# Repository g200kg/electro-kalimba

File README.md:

# electro-kalimba
ElectroKalimba EK-002

## About Kalimba

The kalimba is an African folk instrument. It is a simple instrument that is also called a "thumb piano" and produces sound by plucking metal pieces lined up on a board with your fingers. There are various styles and names depending on the country and region,  but the one with 17 keys is generally distributed as "kalimba" today.  

The keys are arranged so that the pitch is the lowest in the center, and the pitch becomes higher as you move toward the edges, alternating left and right. On the piano, there are only white keys, and there are no keys on the keyboard that correspond to the semitones of the black keys. 

The current kalimba produces a clear, almost sine-wave, music box-like sound from the vibrating metal pieces, but the original use of the kalimba was to add a jittery noise by wrapping a bit of wire around the metal pieces.

---

カリンバはアフリカの民族楽器で、板の上に並んだ金属片を指ではじいて音を出す「親指ピアノ」などとも呼ばれるシンプルな楽器です。国や地方によって様々な様式や名前のものがありますが、現在一般的には 17 鍵のものが「カリンバ」として流通しています。  

キーの配置は中心が一番低い音程になっていて左右交互に端に行くにしたがって高い音になっていきます。音程はピアノで言えば白鍵のみしかなく、黒鍵の半音に相当する鍵盤はありません。  

現在のカリンバは金属片が振動するほぼサイン波の澄んだオルゴールのような音が鳴りますが、元々のカリンバの使い方としては金属片に少し針金を巻きつけるなどによってジージーと鳴るノイズを加えたりします。

## Usage

This "ElectroKalimba" can be played like a normal kalimba, but while a normal kalimba makes a sound by flicking a key, this electronic kalimba makes a sound when you press a key, so the feeling of playing is slightly different.

If nothing is connected to the LineOut terminal, sound will be output from the built-in speaker. The built-in speaker is muted when the LineOut terminal is used. Connect a 2-pole (monaural) or 3-pole (stereo) mini plug to the LineOut terminal. If you connect a plug with 4 or more pins, it may not work properly.

The battery is rechargeable. Charging is done using the Charge MicroUSB terminal on the front of the main unit. The Debug MicroUSB at the top left of the main unit is the USB connector of the Nucleo board used internally, and is used when writing/debugging programs.

---

この ElectroKalimba は普通のカリンバのように演奏できますが、普通のカリンバがキーをはじいて音を出すのに対し、この電子カリンバはキーを押し込んだ時に音を出しますので、演奏の感覚は微妙に異なるかも知れません。

LineOut 端子に何も接続していない場合は内蔵スピーカーから音がでます。LineOut 端子使用時は内蔵スピーカーはミュートされます。LineOut 端子には 2 極(モノラル)または 3 極 (ステレオ) のミニプラグを接続してください。4 極以上のプラグを接続した場合は正常に動作しない場合があります。

電池は充電式です。充電は本体手前にある Charge MicroUSB 端子で行います。本体左上にある Debug MicroUSB は内部で使用している Nucleo ボードの USB コネクタで、プログラムの書き込み/デバッグを行う際に使用します。

| 端子            | 説明                              |
|:---------------:|:---------------------------------:|
| Charge MicroUSB | 充電用 USB                        |
| Debug MicroUSB  | プログラム書き込み/デバッグ用 USB |
| Power Switch    | 電源スイッチ                      |
| Tuning          | チューニング                      |
| Waveform        | 音色設定　詳細は下の図            |
| Sustain         | サステイン　音の伸び方の設定      |
| Volume          | 音量設定                          |
| Line Out        | ライン出力                        |

## Demo Movie  

https://youtu.be/vXB684UsEok  

# Repository

This repository contains design data for the musical instrument "ElectroKalimba".
Contains schematic, software source code, and 3D data of mechanical design.

---

このリポジトリは楽器、"電子カリンバ" の設計データです。
回路図、ソフトウェアのソースコード、機構設計の 3D データを含みます。

# Directories

Contains the following files  
  
   Blender - Mechanism design data - Blender 4.0.2  
   KiCad - Circuit/Board Design Data - KiCad 7.0  
   STM32CubeIDE - Software Design Data - STM32CubeIDE 1.13.2  

---

以下のファイルが含まれています
  
  Blender - 機構設計データ - Blender 4.0.2  
  KiCad - 回路/基板設計データ - KiCad 7.0  
  STM32CubeIDE - ソフトウェア設計データ - STM32CubeIDE 1.13.2  

## Blender files

The Blender directory contains 3D data for the "Blender" housing. The following four parts are required for the casing.  
  
Case_Top: Keyboard section and top of main body  
Case_Mid: Lower part of the main body  
Case_SP_Ring: Speaker front cover  
Case_Bottom: Bottom  
Case_SP_Cap: Speaker bottom cover  

All parts can be printed with no or very little support. When printing Case_Top, Case_Mid, and Case_SP_Ring, rotate them upside down. Printing confirmed with Creality K1 without brim or raft.  

In the design data, numerical values are specified in "cm" units. Please scale as necessary when printing.  

The "*.stl" file is an STL export of each part, already scaled to "mm" units.  

The 3D printer must be able to print at least 140 x 147 mm.  

---

Blender ディレクトリには "Blender" 用の筐体の 3D データが収められています。
筐体として必要なのは次の4つのパーツになります。

* Case_Top : 鍵盤部と本体上部
* Case_Mid : 本体下部
* Case_SP_Ring : スピーカー前面のカバー
* Case_Bottom : 底面
* Case_SP_Cap : スピーカー底部のカバー

全てのパーツはサポートなし、あるいはほぼサポートなしで印刷できま\す。Case_Top、Case_Mid、Case_SP_Ring は印刷時には回転して上下を逆にしてください。
Creality K1 でブリム、ラフトなしで印刷を確認しています。

設計データ上は "cm" 単位で数値指定しています。印刷時に必要に応じてスケーリングしてください。

"*.stl" ファイルは各パーツを STL として書き出したもので、既にスケーリングされて "mm" 単位になっています。

3D プリンターは少なくとも 140 x 147 mm のサイズを造形できる必要があります。

## KiCad files

PDF 化した回路図 と KiCad 7.0.2 用のファイルです。

---

Schametic PDF and files for KiCad 7.0.2.

* EK002-pcb.pdf Schematic PDF.
* EK002.kicad_sch Kicad Schematic
* EK002.kicad_pcb Kicad Artwork

## STM32CubeIDE files

Files for STM32CubeIDE 1.13.2

* EK002.ioc  

STM32CubeIDE (STM32CubeMX) allows you to assign peripheral functions to STM32 pins using a GUI editor, and *.ioc files are the data necessary for this.

---

STM32CubeIDE (STM32CubeMX) では STM32 のピンにペリフェラルの機能を割り当てる作業を GUI エディタで行う事ができ、*.ioc ファイルはそれに必要なデータです。

* main.c

This is the main body of the process.

---

処理の本体です。

### Software Environment

* Prepare STM32CubeIDE as a development environment.
   > [https://www.st.com/en/development-tools/stm32cubeide.html](https://www.st.com/en/development-tools/stm32cubeide.html)
* Software can be written by connecting a PC to the debugging USB port (Micro USB) on the top left of EK002.
* The target of the project is "Nucleo STM32F303K8". To create a project, select `EK002.ioc` in 'File' - 'New' - 'STM32Project from an existing STM32CubeMX Configuration file (*.ioc)' in STM32CubeIDE, and create a new project. I think it is easy to overwrite `Core/Src/main.c` with this `main.c`.
* Serial port can be used for `printf` debugging. Start the appropriate terminal software on the PC connected via USB and connect to STLink Virtual COM Port at 115200 bps.

---

* 開発環境として STM32CubeIDE を用意してください。
  > [https://www.st.com/ja/development-tools/stm32cubeide.html](https://www.st.com/ja/development-tools/stm32cubeide.html)
* PC と EK002 の左上にあるデバッグ用 USB ポート (Micro USB) を接続してソフトウェアの書き込みができます。
* プロジェクトのターゲットは "Nucleo STM32F303K8"　です。プロジェクトを作成するには、STM32CubeIDE の 'File' - 'New' - 'STM32Project from an existing STM32CubeMX Configuration file (*.ioc)' で `EK002.ioc` を選択してプロジェクトを新たに作成し、`Core/Src/main.c` をこの `main.c` で上書きしてしまうのが簡単だと思います。
* シリアルポートを `printf` デバッグ用に使用できます。USB を接続した PC で適当な端末ソフトを起動し、STLink Virtual COM Port に 115200 bps で接続してください。

### Pin Assign

The usage of each pin of STM32 is as follows. Note that some pins are connected to other pins and LEDs within his Nucleo board.

---

STM32 の各ピンの使用状況は以下の通りです。幾つかのピンは Nucleo ボード内で他のピンや LED に接続されている事に注意が必要です。

| Port  | STM32 Pin | Nucleo Pin | Function in EK-002        |
|:-----:|:---------:|:----------:|:-------------------------:|
| PA_0  |     6     |     A0     | ADC1 IN1 (POT2)           |
| PA_1  |     7     |     A1     | ADC1 IN2 (POT3)           |
| PA_2  |     8     |     A7     | -                         |
| PA_3  |     8     |     A2     | ADC1 IN4 (POT4)           |
| PA_4  |    10     |     A3     | DAC1 OUT1 (AudioOut)      |
| PA_5  |    11     |     A4(D5) | - (conn. to PB6 w/SB16)   |
| PA_6  |    12     |     A5(D4) | - (conn. to PB7 w/SB18)   |
| PA_7  |    13     |     A6     | TIM17 CH1                 |
| PA_8  |    18     |     D9     | KeyScan Out 1             |
| PA_9  |    19     |   D1/TX    | -                         |
| PA_10 |    20     |   D0/RX    | -                         |
| PA_11 |    21     |    D10     | KeyScan Out 2             |
| PA_12 |    22     |     D2     | KeyScan Out 0             |
| PA_13 |    23     |      -     | (SWDIO)                   |
| PA_14 |    24     |      -     | (SWCLK)                   |
| PA_15 |    25     |      -     | -                         |
| PB_0  |    14     |     D3     | KeyScan In 0              |
| PB_1  |    15     |     D6     | KeyScan In 1              |
| PB_2  |     -     |      -     | -                         |
| PB_3  |    26     |   D13(LED) | -                         |
| PB_4  |    27     |    D12     | KeyScan In 2              |
| PB_5  |    28     |    D11     | KeyScan In 3              |
| PB_6  |    29     |   D5(A4)   | KeyScan In 4  (PA5 w/SB16)|
| PB_7  |    30     |   D4(A5)   | KeyScan In 5  (PA6 w/SB18)|
| PF_0  |     2     |     D7     | -                         |
| PF_1  |     3     |     D8     | -                         |

### Peripheral Assign

Peripherals such as Timers and DMA are used as follows.

---

STM32 の タイマーや DMA 等のペリフェラルは以下のように使用されています。

| Timing  | Data Source    |   DMA    |Data Destination | 
|:-------:|:--------------:|:--------:|:---------------:|
| TIM6    | outBuff[]      | DMA1 Ch3 | DAC1 Ch1        |
| TIM7    | KeyScan        | -        | software        |
| TIM17   | neoPixelBuff[] | DMA1 Ch7 | NeoPixel LED    |
| -       | ADC1 Ch1/2/4   | DMA1_Ch1 | adcVal[]        |

### POT

POT1 is fixed in the circuit as the Volume knob. The three POT2-POT4 are read by ADC (ADC1 Ch1/2/4) and processed by software.
Reading is done by DMA (DMA1 Ch1) and is always stored in the variable `adcVal[]`.

---

POT1 は Volume ツマミとして回路的に固定されています。POT2-POT4 の 3 つは ADC (ADC1 Ch1/2/4) によって読み込まれソフトウェア的に処理されます。
読み込みは DMA (DMA1 Ch1) で行われ、常時、変数 `adcVal[]` に取り込まれています。

### Key Scan

Keyboard scanning is performed by reading the state of KeyScan In 0-5 when any one of KeyScan Out 0-2 is output.

---

鍵盤のスキャンは KeyScan Out 0-2 のどれか一つを出力した時の KeyScan In 0-5 の状態を読み込む事で行います。

### Generate

Signal generation is done with the `generate()` function, which fills half the size (first or second half) of `outBuff[]` in one call.

The number of voices that can be played simultaneously is 4. The pressed key is assigned to an empty (or less important) voice. Also, when assigning a new sound to a voice that is currently sounding, reduce the volume of the voice that is currently sounding before assigning it to avoid noise.

The audio signal is generated by mixing the four waveform tables `waveTabA` - `waveTabD` and the fixed frequency ring modulator signal. The signal mix changes as follows depending on the value of the Waveform (adcVal[1]) knob.

---

信号の生成は `generate()` 関数で行い、1回の呼び出しで `outBuff[]` の半分のサイズ (前半または後半) を埋めます。

同時発音可能なボイス数は 4 です。押された鍵盤から空いている (または重要度の低い) ボイスに割り当てています。 また、現在発音中のボイスに新たな音を割り当てる際にはノイズを発生させないように発音中のボイスの音量を絞ってから割り当てるようにします。

音声信号は波形テーブル `waveTabA` - `waveTabD` の 4つのテーブルと固定周波数のリングモジュレータの信号をミックスして生成します。Waveform (adcVal[1]) のツマミの値で次のように信号のミックスが変わります。

| Waveform | 説明                                            |
|:--------:|:-----------------------------------------------:|
|     0 => 1024 | waveTabA (Sine) => waveTabB (Sawtooth)     |
|  1024 => 2048 | waveTabB (Sawtooth) => waveTabC (Pulse)    |
|  2048 => 3072 | waveTabC (Pulse) => waveTabD (Square)      |
|  3072 => 4096 | waveTabD (Square) => RingMod               |

waveTabA (pure Sin) => waveTabB (Sawtooth) => waveTabC (Pulse) => => waveTabD (Square) => ring mod

各テーブルは次のような波形になっています。

またエンベロープは envTab[] が表すカーブに従って発音開始から音量が下がっていきます。

### Output

The generated audio signal is constantly sent to the DAC from the buffer outBuff[] by DMA (DMA1 Ch3). DMA generates an interrupt when half or all of the buffer size has been sent, so the interrupt is used as a trigger to fill the first or second half of the buffer with the next signal.

---

生成された音声信号はバッファ outBuff[] から DMA (DMA1 Ch3) によって DAC に常時送られます。DMA はバッファサイズの半分、および全部を送り終わった時に割り込みを発生しますので、割り込みの時点をトリガーにして送り終わった前半または後半のバッファを次の信号で埋めて行きます。

### NeoPixel

NeoPixel is a full color LED driven by a serial signal. It is difficult to create the timing of the control signal with software alone, so we use the PWM generation function of the timer (TIM17).
creating a signal. `neoPixelBuff[]` has an array of byte data representing the PWM pulse width, and it controls the four NeoPixel LEDs by sequentially sending it to the PWM generation function attached to the timer using DMA.

---

NeoPixel はシリアル信号で駆動するフルカラー LED です。ソフトウェアだけで制御信号のタイミングを作るのは困難ですのでタイマー (TIM17) の PWM 生成機能で
信号を作っています。`neoPixelBuff[]` には PWM のパルス幅を表すバイトデータの配列があり、DMA でタイマーに付随する PWM 発生機能に順次送る事により、4 つの NeoPixel LED を制御しています。

### Actual Current Consumption Test

800mAh 9V 電池使用時の電流測定と動作時間見積

| Current      | Condition          | Estimated operating time<br/>(800mAh Batt) |  
|:------------:|:------------------:|:------------------------:|
| 80mA - 100mA | Lineout            | 10h - 8h                 |
| 90mA - 120mA | Speaker Voluem Max | 8.9h -  6.7h             |

# License

The files in this repository are released under the MIT license.

---

このリポジトリのファイルは MIT ライセンスのもとに公開されています。

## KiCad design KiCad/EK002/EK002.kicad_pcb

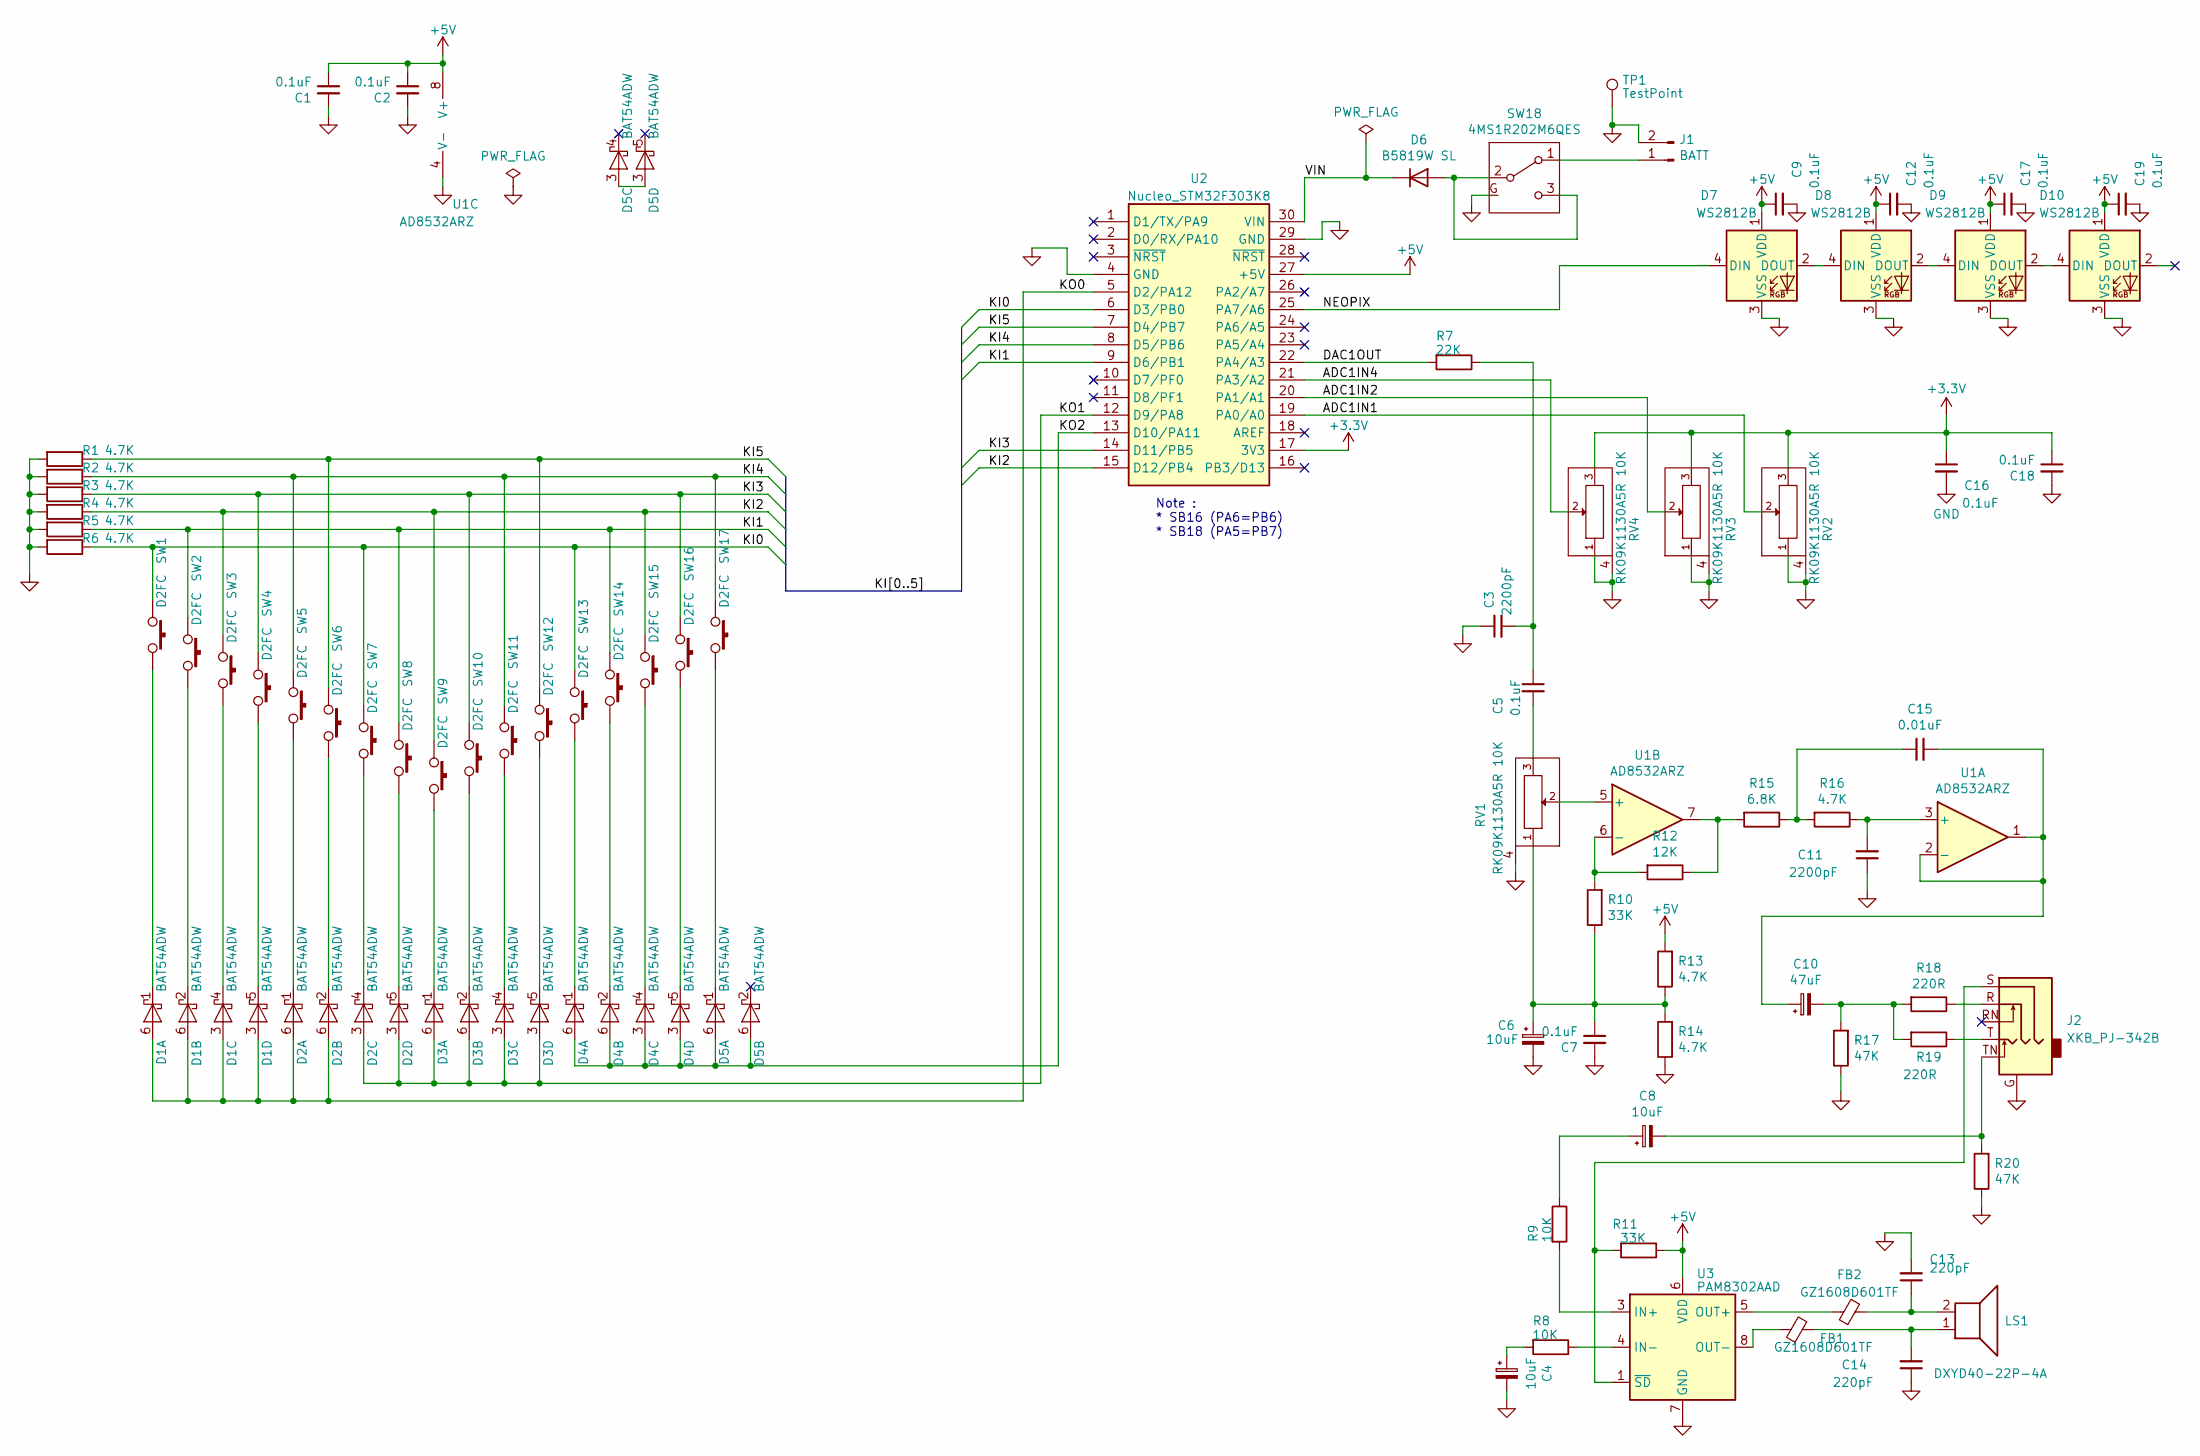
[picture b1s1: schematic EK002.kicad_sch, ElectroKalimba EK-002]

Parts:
C1, C2, C5, C7, C9, C12, C16, C17, C18, C19: 0.1uF; C_0603_1608Metric
C3, C11: 2200pF; C_0603_1608Metric
C4, C6, C8: 10uF; CP_EIA-3216-18_Kemet-A
C10: 47uF; CP_EIA-3528-21_Kemet-B
C13, C14: 220pF; C_0603_1608Metric
C15: 0.01uF; C_0603_1608Metric
D1, D2, D3, D4, D5: BAT54ADW; SOT-363_SC-70-6
D6: B5819W SL; D_SOD-123
D7, D8, D9, D10: WS2812B; LED_WS2812B_PLCC4_5.0x5.0mm_P3.2mm
FB1, FB2: GZ1608D601TF; L_0603_1608Metric
J1: BATT; PinSocket_1x02_P2.54mm_Horizontal
J2: XKB_PJ-342B; Jack_3.5mm_XKB_PJ342B-TX
LS1: DXYD40-22P-4A; PinSocket_1x02_P2.54mm_Horizontal
R1, R2, R3, R4, R5, R6, R13, R14, R16: 4.7K; R_0603_1608Metric
R7: 22K; R_0603_1608Metric
R8, R9: 10K; R_0603_1608Metric
R10, R11: 33K; R_0603_1608Metric
R12: 12K; R_0603_1608Metric
R15: 6.8K; R_0603_1608Metric
R17, R20: 47K; R_0603_1608Metric
R18, R19: 220R; R_0603_1608Metric
RV1, RV2, RV3, RV4: RK09K1130A5R 10K; Potentiometer_Alps_RK09K_Single_Vertical
SW1, SW2, SW3, SW4, SW5, SW6, SW7, SW8, SW9, SW10, SW11, SW12, SW13, SW14, SW15, SW16, SW17: D2FC; Sw_Micro_Omron-D2F
SW18: 4MS1R202M6QES; Sw_Rocker_4MS1R202M6QES
TP1: TestPoint; PinHeader_1x01_P2.54mm_Vertical
U1: AD8532ARZ; SOIC-8_3.9x4.9mm_P1.27mm
U2: Nucleo_STM32F303K8; Nucleo_32
U3: PAM8302AAD; SOP-8_3.9x4.9mm_P1.27mm

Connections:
+3.3V: C16.1, C18.1, RV2.3, RV3.3, RV4.3, U2.17 (3V3)
+5V: C1.1, C2.1, C9.1, C12.1, C17.1, C19.1, D7.1 (VDD), D8.1 (VDD), D9.1 (VDD), D10.1 (VDD), R11.1, R13.2, U1.8 (V+), U2.27 (+5V), U3.6 (VDD)
/ADC1IN1: RV2.2, U2.19 (PA0/A0)
/ADC1IN2: RV3.2, U2.20 (PA1/A1)
/ADC1IN4: RV4.2, U2.21 (PA3/A2)
/DAC1OUT: R7.2, U2.22 (PA4/A3)
/KI0: R6.1, SW1.C, SW7.C, SW13.C, U2.6 (D3/PB0)
/KI1: R5.1, SW2.C, SW8.C, SW14.C, U2.9 (D6/PB1)
/KI2: R4.1, SW3.C, SW9.C, SW15.C, U2.15 (D12/PB4)
/KI3: R3.1, SW4.C, SW10.C, SW16.C, U2.14 (D11/PB5)
/KI4: R2.1, SW5.C, SW11.C, SW17.C, U2.8 (D5/PB6)
/KI5: R1.1, SW6.C, SW12.C, U2.7 (D4/PB7)
/KO0: D1.3 (A), D1.6 (A), D2.6 (A), U2.5 (D2/PA12)
/KO1: D2.3 (A), D3.3 (A), D3.6 (A), U2.12 (D9/PA8)
/KO2: D4.3 (A), D4.6 (A), D5.6 (A), U2.13 (D10/PA11)
/NEOPIX: D7.4 (DIN), U2.25 (PA7/A6)
/VIN: D6.1 (K), U2.30 (VIN)
GND: C1.2, C2.2, C3.1, C4.2, C6.2, C7.2, C9.2, C11.1, C12.2, C13.2, C14.1, C16.2, C17.2, C18.2, C19.2, D7.3 (VSS), D8.3 (VSS), D9.3 (VSS), D10.3 (VSS), J1.2, J2.G, R1.2, R2.2, R3.2, R4.2, R5.2, R6.2, R14.1, R17.1, R20.1, RV1.4 (G), RV2.1, RV2.4 (G), RV3.1, RV3.4 (G), RV4.1, RV4.4 (G), SW18.G, TP1.1, U1.4 (V-), U2.4 (GND), U2.29 (GND), U3.7 (GND)
unnamed: C3.2, C5.1, R7.1
unnamed: C4.1, R8.2
unnamed: C5.2, RV1.3
unnamed: C6.1, C7.1, R10.1, R13.1, R14.2, RV1.1
unnamed: C8.1, R9.1
unnamed: C8.2, J2.TN, R20.2
unnamed: C10.2, R17.2, R18.2, R19.2
unnamed: C13.1, FB2.2, LS1.2
unnamed: C14.2, FB1.2, LS1.1
unnamed: C15.1, R15.1, R16.2
unnamed: D1.1 (K), SW1.NO
unnamed: D1.2 (K), SW2.NO
unnamed: D1.4 (K), SW3.NO
unnamed: D1.5 (K), SW4.NO
unnamed: D2.1 (K), SW5.NO
unnamed: D2.2 (K), SW6.NO
unnamed: D2.4 (K), SW7.NO
unnamed: D2.5 (K), SW8.NO
unnamed: D3.1 (K), SW9.NO
unnamed: D3.2 (K), SW10.NO
unnamed: D3.4 (K), SW11.NO
unnamed: D3.5 (K), SW12.NO
unnamed: D4.1 (K), SW13.NO
unnamed: D4.2 (K), SW14.NO
unnamed: D4.4 (K), SW15.NO
unnamed: D4.5 (K), SW16.NO
unnamed: D5.1 (K), SW17.NO
unnamed: D6.2 (A), SW18.2 (B), SW18.3 (C)
unnamed: D7.2 (DOUT), D8.4 (DIN)
unnamed: D8.2 (DOUT), D9.4 (DIN)
unnamed: D9.2 (DOUT), D10.4 (DIN)
unnamed: J1.1, SW18.1 (A)
unnamed: J2.R, R18.1
unnamed: J2.T, R19.1
unnamed: R12.1, R15.2, U1.7
unnamed: C11.2, R16.1, U1.3 (+)
unnamed: C10.1, C15.2, U1.1, U1.2 (-)
unnamed: RV1.2, U1.5 (+)
unnamed: R10.2, R12.2, U1.6 (-)
unnamed: R9.2, U3.3 (IN+)
unnamed: R8.1, U3.4 (IN-)
unnamed: FB2.1, U3.5 (OUT+)
unnamed: FB1.1, U3.8 (OUT-)
unnamed: J2.S, R11.2, U3.1 (~SD)

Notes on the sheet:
Note : * SB16 (PA6=PB6) * SB18 (PA5=PB7)

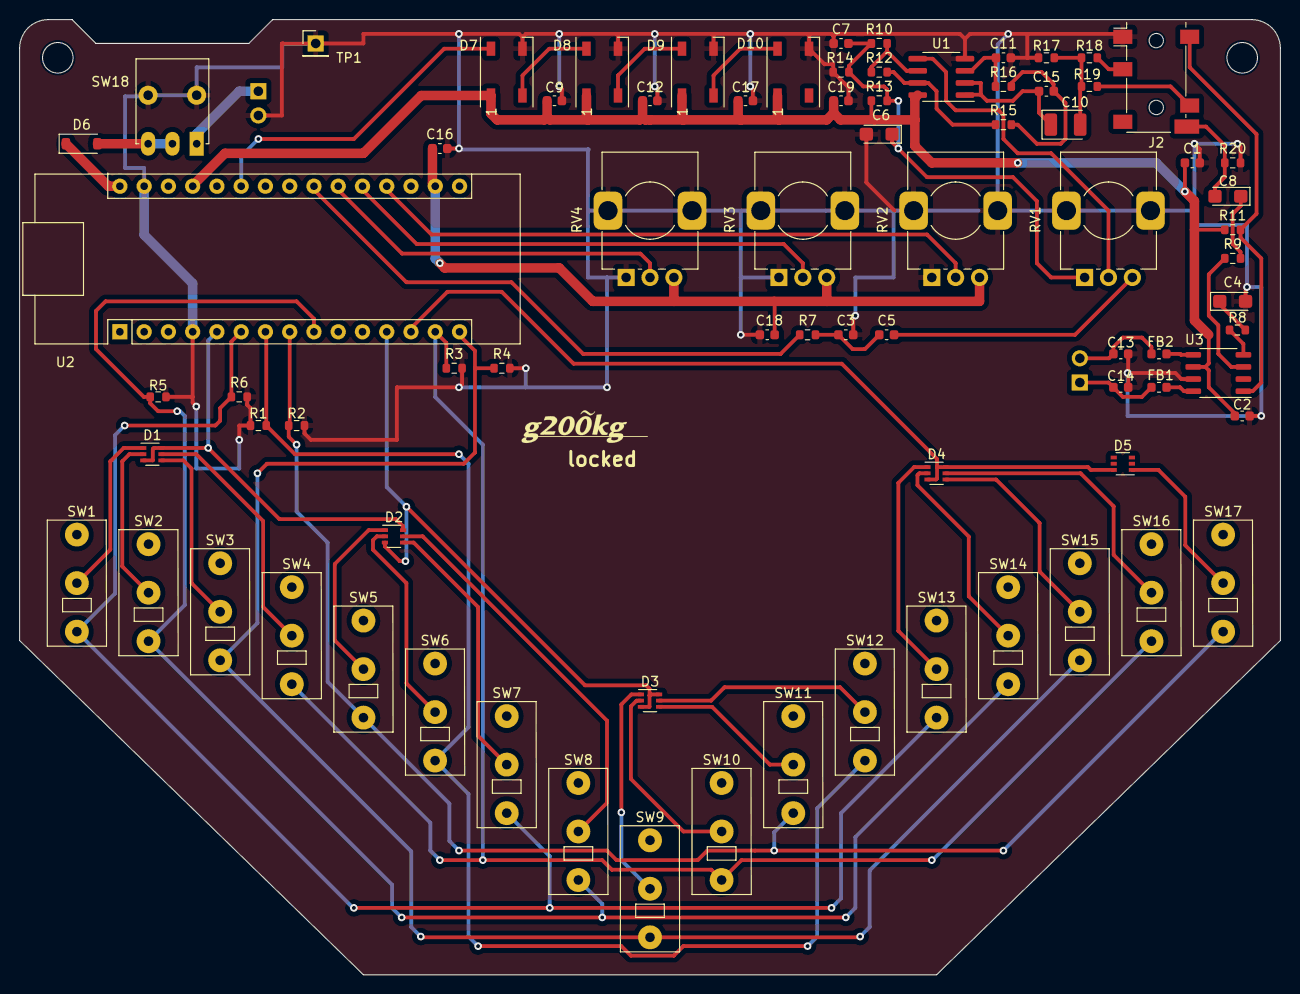
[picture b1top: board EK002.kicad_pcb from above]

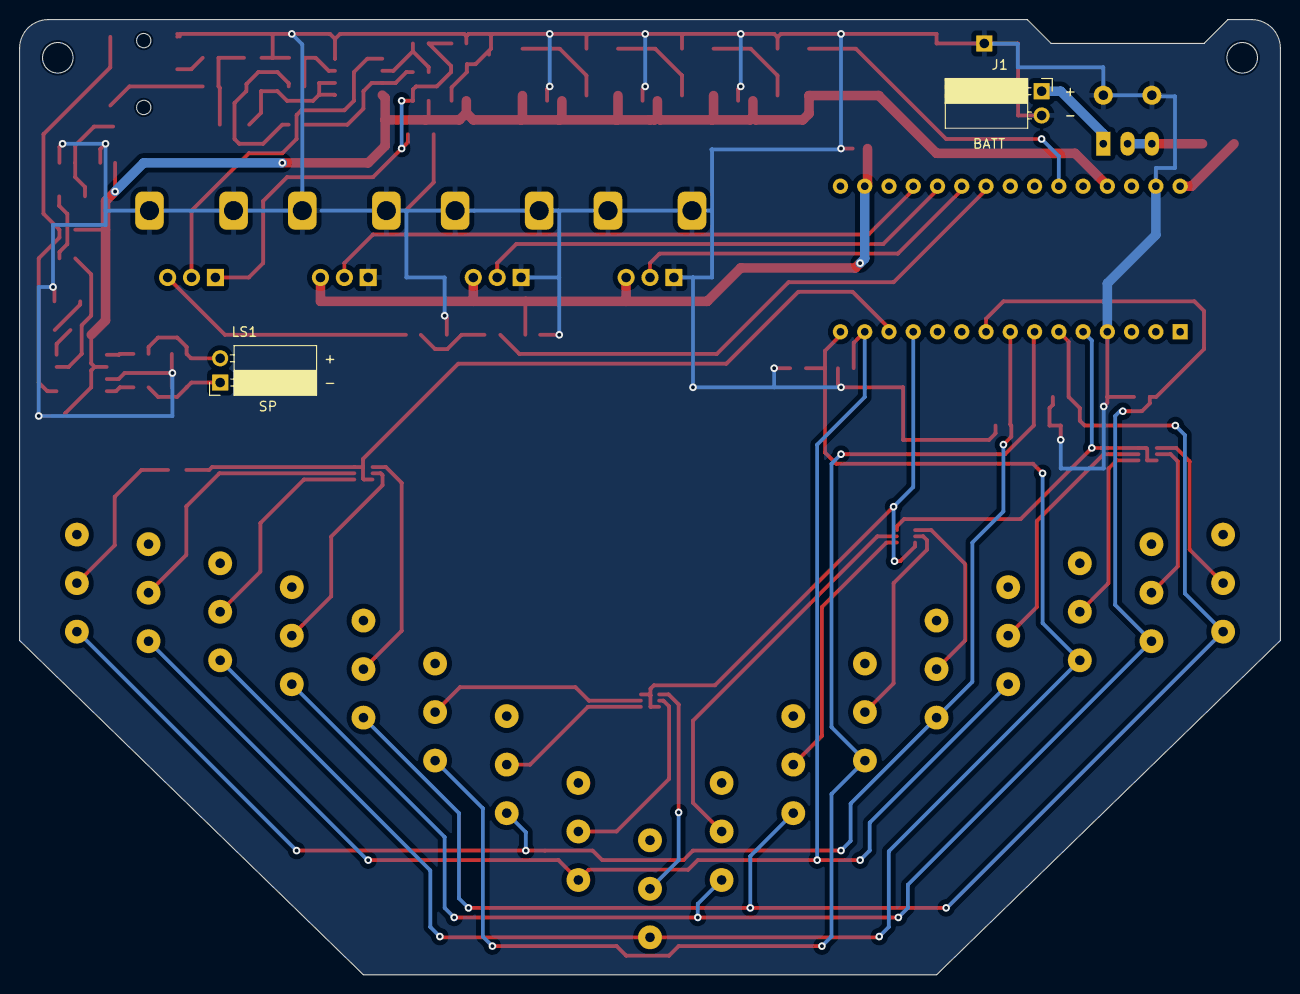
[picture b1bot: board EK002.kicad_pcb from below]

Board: 2 copper layers, 132.0 x 100.0 mm, 82 parts (2 on the bottom side), 62 nets.

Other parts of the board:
 : Hole_PTH_3.2mm
 #2: Hole_PTH_3.2mm

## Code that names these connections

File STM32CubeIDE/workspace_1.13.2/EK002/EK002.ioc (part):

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Mcu.Name=STM32F303K(6-8)Tx
Mcu.Package=LQFP32
Mcu.UserName=STM32F303K8Tx
PA0.Mode=IN1-Single-Ended
PA0.Signal=ADC1_IN1
PA1.Mode=IN2-Single-Ended
PA1.Signal=ADC1_IN2
PA11.Signal=GPIO_Output
PA12.Signal=GPIO_Output
PA13.GPIOParameters=GPIO_Label
PA13.GPIO_Label=SWDIO
PA13.Mode=Trace_Asynchronous_SW
PA13.Signal=SYS_JTMS-SWDIO
PA14.GPIOParameters=GPIO_Label
PA14.GPIO_Label=SWCLK
PA14.Mode=Trace_Asynchronous_SW
PA14.Signal=SYS_JTCK-SWCLK
PA15.GPIOParameters=GPIO_Label
PA15.GPIO_Label=VCP_RX
PA15.Mode=Asynchronous
PA15.Signal=USART2_RX
PA2.GPIOParameters=GPIO_Label
PA2.GPIO_Label=VCP_TX
PA2.Mode=Asynchronous
PA2.Signal=USART2_TX
PA3.Mode=IN4-Single-Ended
PA3.Signal=ADC1_IN4
PA4.Signal=COMP_DAC11_group
PA7.Signal=S_TIM17_CH1
PA8.Signal=GPIO_Output
PB0.Signal=GPIO_Input
PB1.Signal=GPIO_Input
PB3.Mode=Trace_Asynchronous_SW
PB3.Signal=SYS_JTDO-TRACESWO
PB4.Signal=GPIO_Input
PB5.Signal=GPIO_Input
PB6.Signal=GPIO_Input
PF0\ /\ OSC_IN.GPIOParameters=GPIO_Label
PF0\ /\ OSC_IN.GPIO_Label=MCO
PF0\ /\ OSC_IN.Mode=HSE-External-Clock-Source
PF0\ /\ OSC_IN.Signal=RCC_OSC_IN
PF1\ /\ OSC_OUT.Signal=GPIO_Output
RCC.HSEPLLFreq_Value=8000000
RCC.HSE_VALUE=8000000
RCC.SYSCLKFreq_VALUE=64000000
RCC.SYSCLKSourceVirtual=RCC_SYSCLKSOURCE_PLLCLK
board=NUCLEO-F303K8
boardIOC=true

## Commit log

2023-12-06 add files
2023-12-06 Add contents of main.c
2023-12-09 update 3d models
2023-12-13 update 3d model / software
2023-12-13 add tables
2023-12-13 update readme/wavetable
2023-12-14 add movie link
2023-12-18 update 3d model
2023-12-20 add anti-chattering / update 3D model
